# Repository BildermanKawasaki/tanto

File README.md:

# tanto

a 21 key mechanical keyboard by Bild

 [View Layout in KLC](https://keyboard-layout-creator.com/layout/cmlz817of007qp2015syvq61z)

[View PCB in Kicanvas](https://kicanvas.org/?repo=https%3A%2F%2Fgithub.com%2FBildermanKawasaki%2Ftanto%2Ftree%2Fmain%2FPCB)

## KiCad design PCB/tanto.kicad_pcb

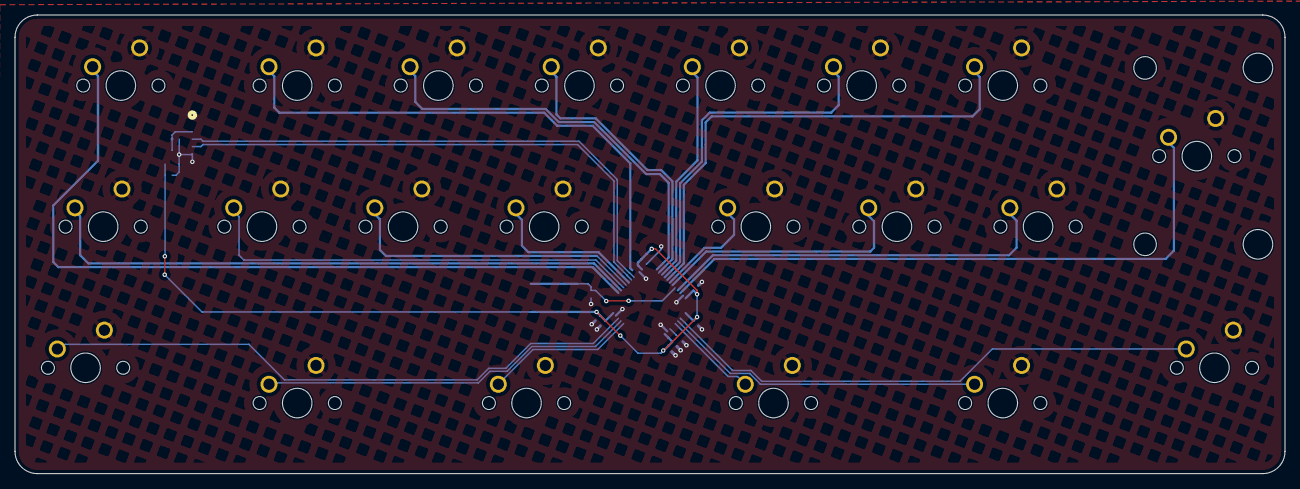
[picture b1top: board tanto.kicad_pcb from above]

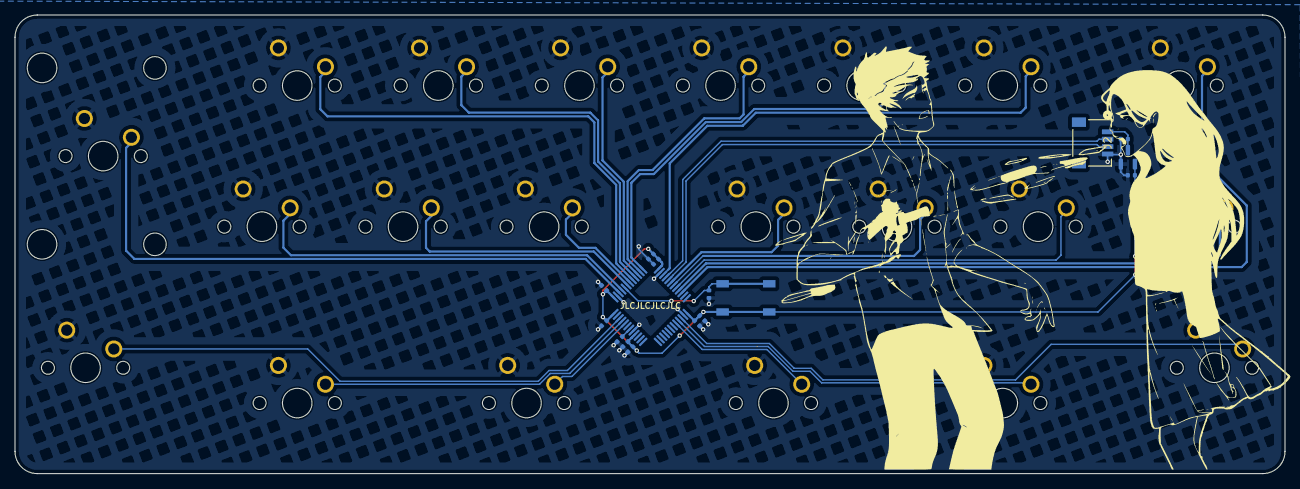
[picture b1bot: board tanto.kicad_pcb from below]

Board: 4 copper layers, 171.5 x 61.9 mm, 37 parts (16 on the bottom side), 28 nets.

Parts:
C7, C10, C11, C13, C16: 100nF; Capacitor_0402
C8, C9, C15: 1uF; Capacitor_0402
C12, C17: 4.7uF; Capacitor_0402
C14: 10nF; Capacitor_0402
J2: SM04B-SRSS-TB; CONN_SM04B-SRSS-TB_JST
MX1, MX2, MX3, MX4, MX5, MX6, MX7, MX8, MX9, MX10, MX11, MX12, MX13, MX14, MX15, MX16, MX17, MX18, MX19, MX20, MX21: MX_SW_solder; SW_MX_1u
R1: 10k; Resistor_0402
SW1: SW_Push; Button_TL3342
U1: STM32F072CBT6; Package_LQFP-48_7x7mm_P0.5
U3: XC6206; Voltage_SOT-23

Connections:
+3.3V: C9.1, C10.2, C11.2, C12.2, C13.2, C14.2, C15.2, C16.2, C17.2, SW1.1, U1.1 (VBAT), U1.9 (VDDA), U1.24 (VDD), U1.36 (VDDIO2), U1.48 (VDD), U3.2 (VO)
+5V: C8.1, J2.1, U3.3 (VI)
/BOOT0: R1.2, SW1.2, U1.44 (BOOT0)
/MCU_D+: J2.2, U1.33 (PA12)
/MCU_D-: J2.3, U1.32 (PA11)
/NRST: C7.1, U1.7 (NRST)
GND: C7.2, C8.2, C9.2, C10.1, C11.1, C12.1, C13.1, C14.1, C15.1, C16.1, C17.1, J2.4, MX1.2, MX2.2, MX3.2, MX4.2, MX5.2, MX6.2, MX7.2, MX8.2, MX9.2, MX10.2, MX11.2, MX12.2, MX13.2, MX14.2, MX15.2, MX16.2, MX17.2, MX18.2, MX19.2, MX20.2, MX21.2, R1.1, U1.8 (VSSA), U1.23 (VSS), U1.35 (VSS), U1.47 (VSS), U3.1 (GND)
r0c0: MX1.1, U1.27 (PB14)
r0c1: MX2.1, U1.34 (PA13)
r0c2: MX3.1, U1.37 (PA14)
r0c3: MX4.1, U1.38 (PA15)
r0c4: MX5.1, U1.39 (PB3)
r0c5: MX6.1, U1.40 (PB4)
r0c6: MX7.1, U1.41 (PB5)
r1c0: MX9.1, U1.28 (PB15)
r1c1: MX10.1, U1.29 (PA8)
r1c2: MX11.1, U1.30 (PA9)
r1c3: MX12.1, U1.31 (PA10)
r1c4: MX13.1, U1.42 (PB6)
r1c5: MX14.1, U1.43 (PB7)
r1c6: MX15.1, U1.45 (PB8)
r1c7: MX8.1, U1.46 (PB9)
r2c0: MX16.1, U1.22 (PB11)
r2c2: MX17.1, U1.21 (PB10)
r2c3: MX18.1, U1.20 (PB2)
r2c4: MX19.1, U1.5 (PF0)
r2c5: MX20.1, U1.4 (PC15)
r2c7: MX21.1, U1.3 (PC14)

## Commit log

2026-03-22 initial commit of case and PCB files
2026-03-25 PCB and schematic updates
    - added jst-sh connector for UDB compatibility
    - removed USB input protection
    - routed most traces
    - arranged all components
2026-03-25 added kicanvas link to readme
2026-03-25 added klc to readme
2026-03-25 removed unneeded backticks from image embed in README.md
2026-03-26 progress on pcb layout
    - routed remaining traces
    - tidied up routing
    -added ground fill
2026-03-26 fixed DRC errors
2026-03-26 minimized front copper layer signal routing
2026-03-26 added ISO enter stab footprint
2026-03-26 Update links in README for layout and PCB
    - added KLC link
    - changed wording for Kicanvas link
2026-03-26 Add links to keyboard layout and PCB
    added line between KLC screenshot and link
2026-03-26 added silk image
